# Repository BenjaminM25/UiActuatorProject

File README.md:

# Closed-Loop Linear Actuator

> Bachelor project, University of Agder (UiA), 2026
> Custom BLDC motor controller for a leadscrew linear actuator with
> closed-loop position control.

## Overview

This project contains code and production files for a small linear
actuator using the lead screw principle with a custom pcb. The system
consists of a 12 mm BLDC motor with a 1:24 gearbox, integrated hall-
sensors for motor commutation, a AS5600L magnetic encoder module for
position/velocity control. It also supports communication over CAN
and USB-C.

A demonstration video of the actuator can be found here:

[Demonstration video](https://youtube.com/watch?v=XubzCKECgCM)

## Features

- Trapezoidal 3-PWM/6-PWM commutation (Hall-sensor based)
- Closed-loop position control (profiled trajectory + PID)
- Phase current sensing via ADC
- On-chip temperature monitoring with thermal protection
- CAN (FDCAN) communication
- Live telemetry over USB CDC (Teleplotter)

## Hardware

| Component        | Part               |
|------------------|--------------------|
| MCU              | STM32G473RC        |
| Gate driver      | DRV8316 (SPI)      |
| Position encoder | AS5600L (I2C)      |
| Commutation      | Hall sensors       |
| CAN transceiver  | TCAN3403           |
| Motor            | 12 mm BLDC, 1:24   |

## Third Party

The DRV8316 BLDC Driver has been adapted from the[SIMPLEFOC](https://github.com/simplefoc/Arduino-FOC-drivers/tree/master/src/drivers/drv8316) GitHub library.

## Building & flashing

The CubeIDE project contains custom files for the actuator
within Core/Actuator. The DRV8316 driver, hall encoder and
magnetic encoder is found in Drivers/DRV8316.

The .elf file generated in Debug after building the project
is uploaded to the pcb using STM32CubeProgrammer. First time use
of the pcb requires either a ST-Link debugger using swd or
programming USB-C by setting the mcu in the
DFU(device firmware upgrade) mode.

## Disclaimer

Portions of this firmware were developed with the assistance of
AI-generated code. All such content has been reviewed, tested, and
adapted by the author.

## License
This project is licensed under the MIT License — see the [LICENSE](LICENSE) file.

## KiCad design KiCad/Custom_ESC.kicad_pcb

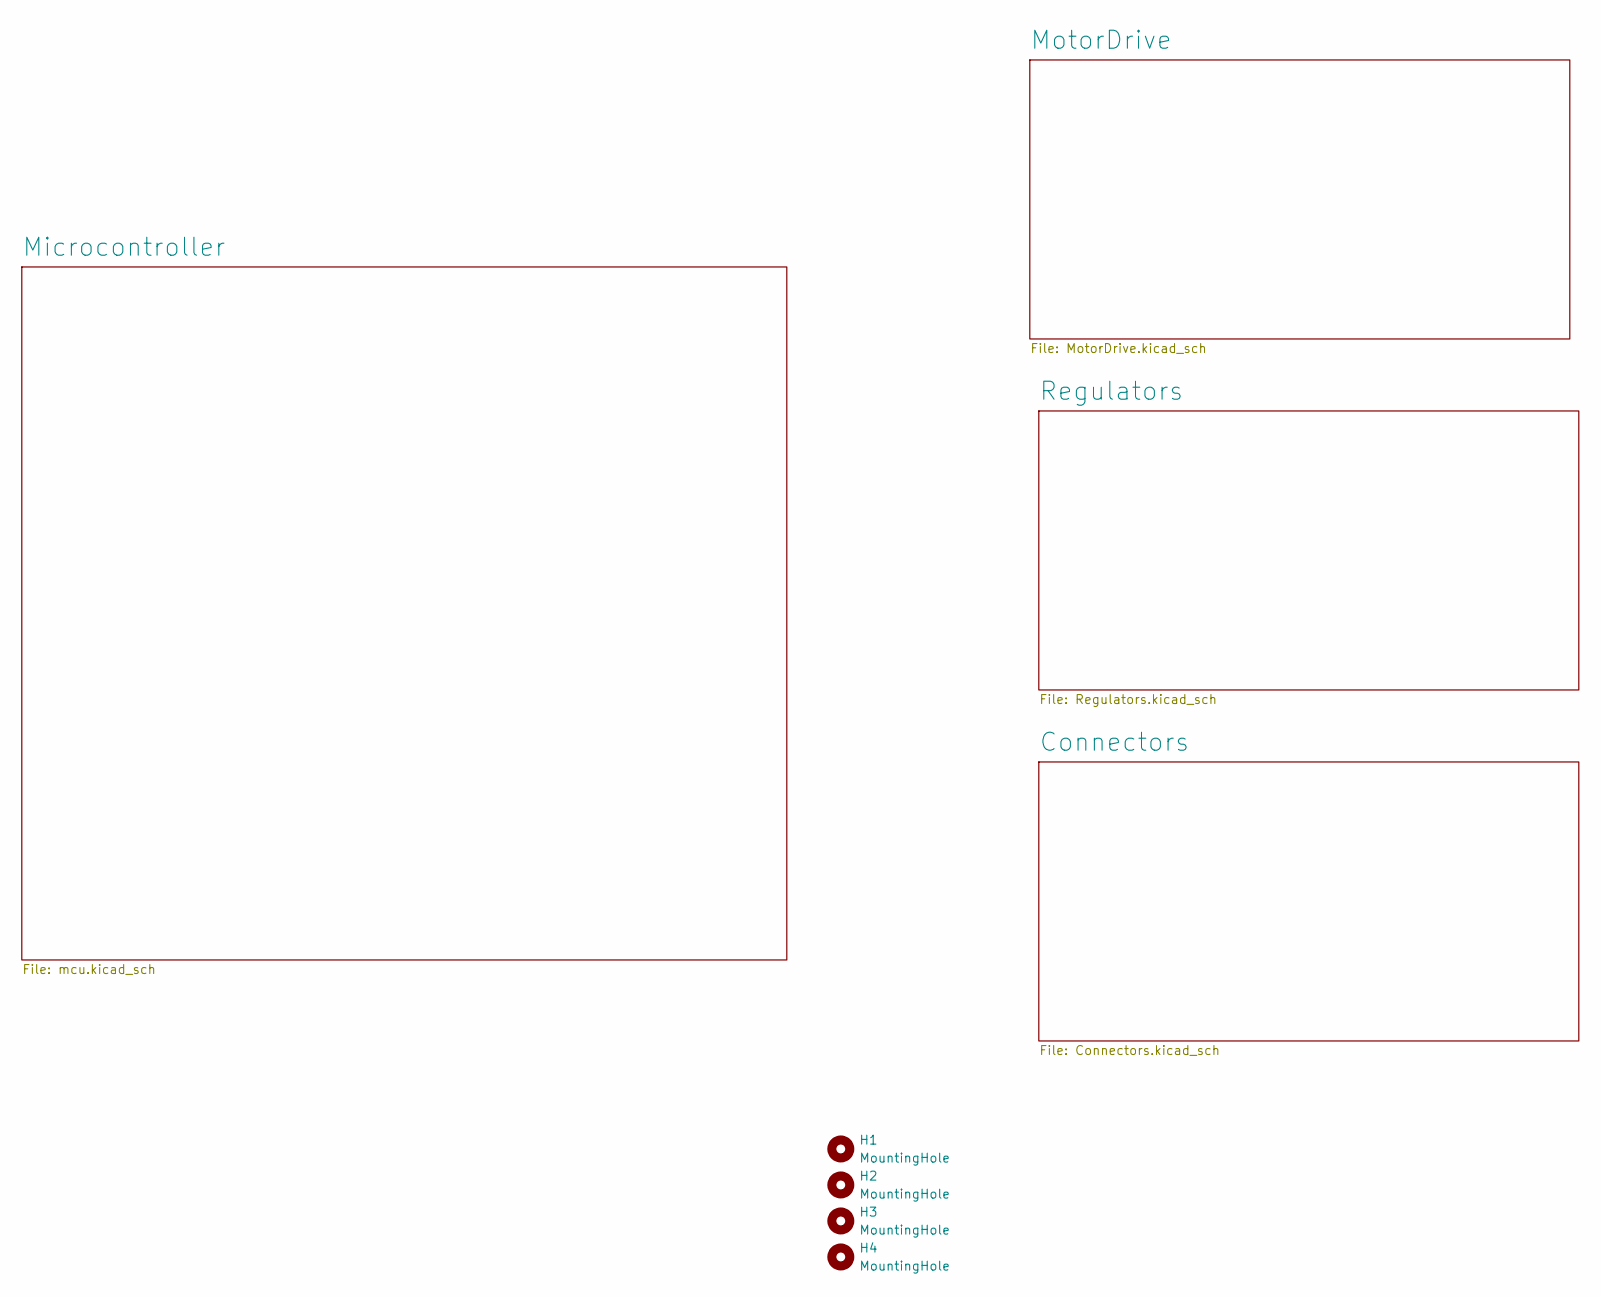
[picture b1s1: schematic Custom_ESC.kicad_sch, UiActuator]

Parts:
H1, H2, H3, H4: MountingHole; MountingHole_2.2mm_M2

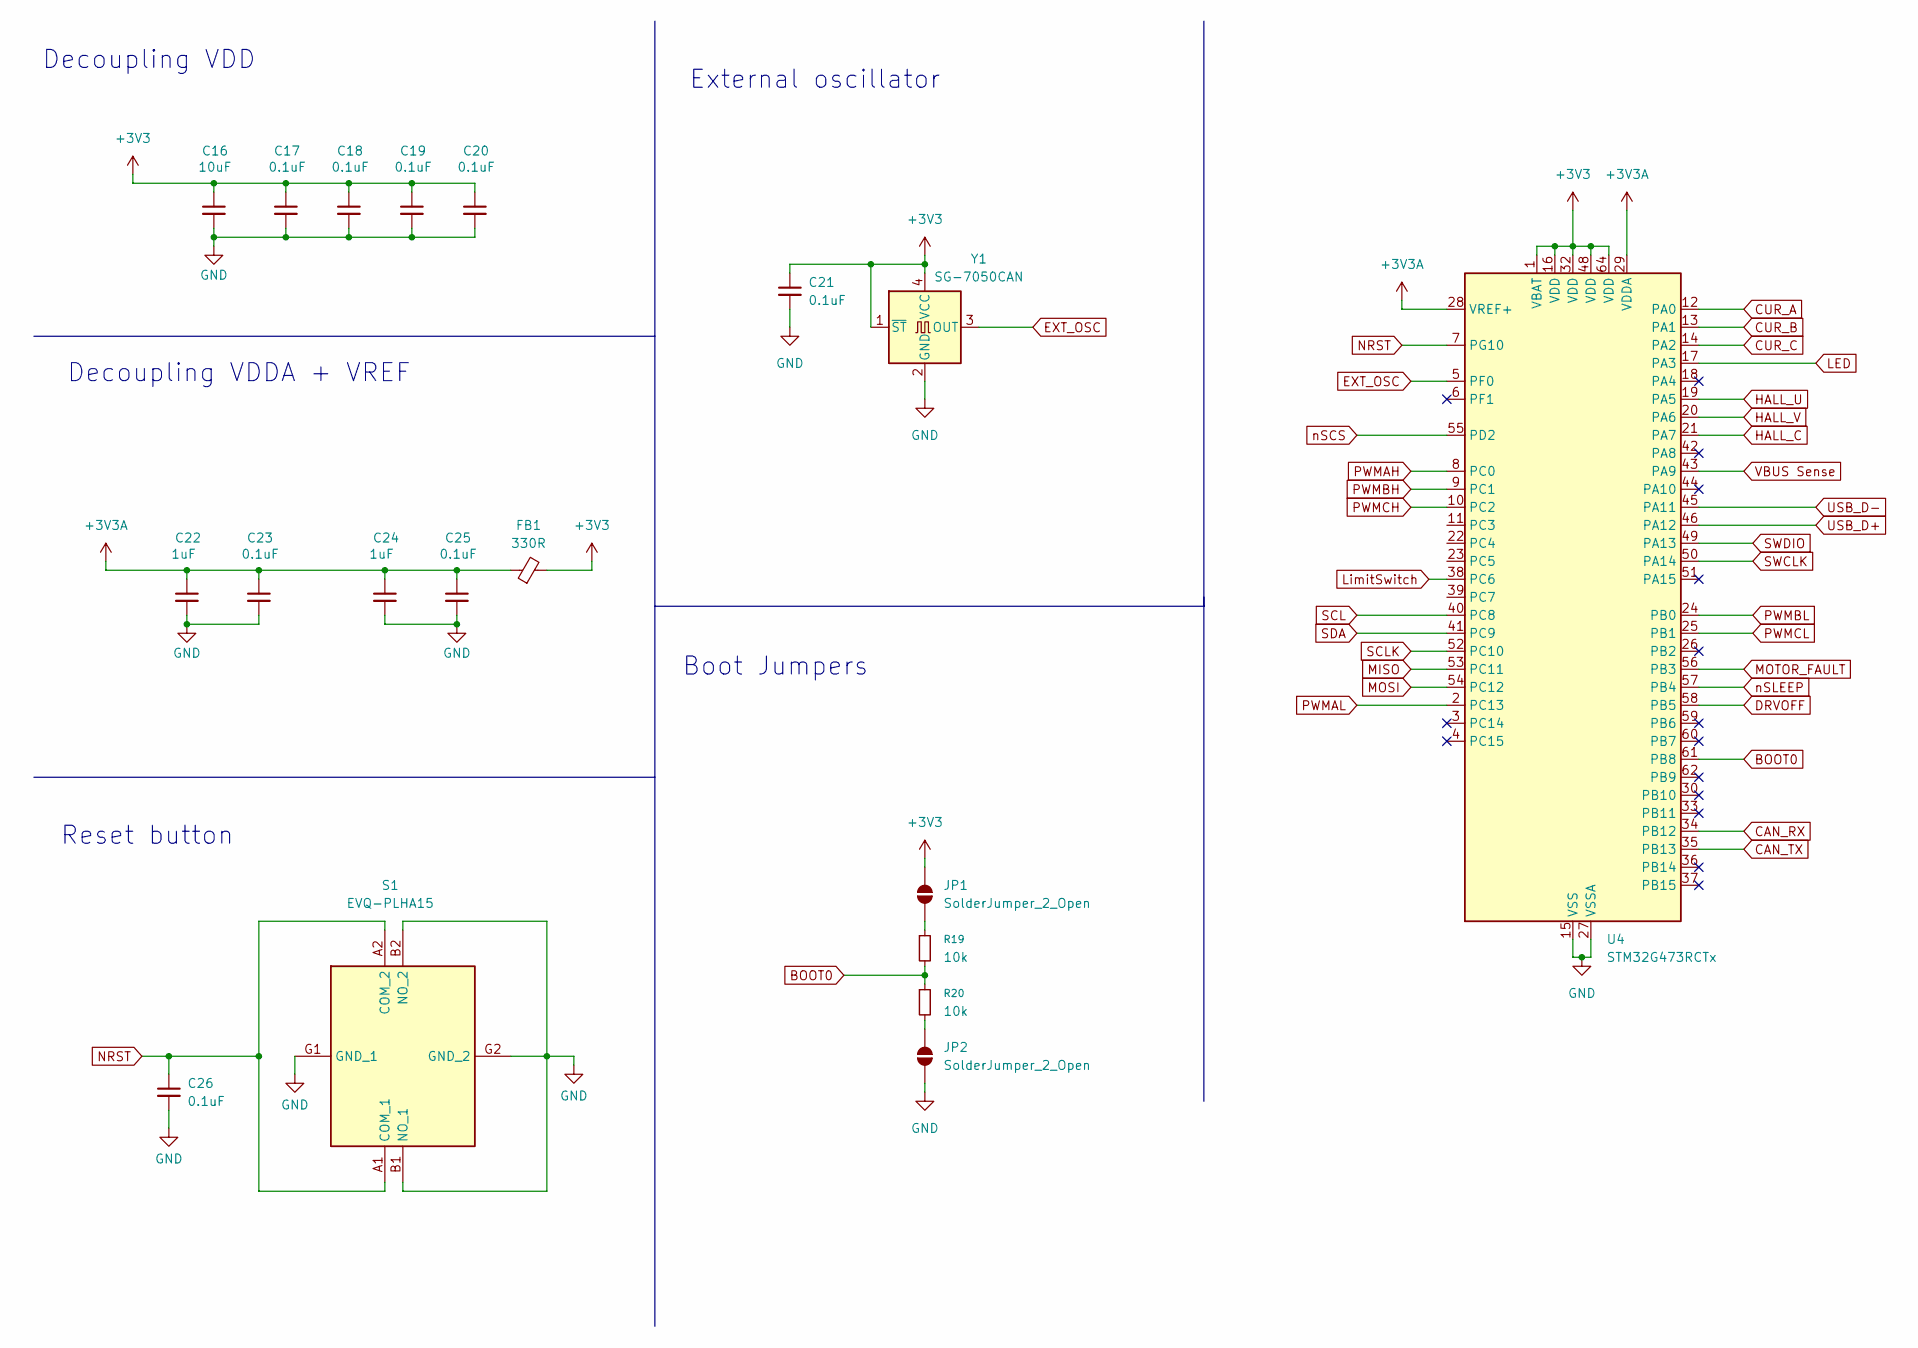
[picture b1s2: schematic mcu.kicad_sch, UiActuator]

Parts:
C16: 10uF; C_0603_1608Metric; LCSC C19702
C17, C18, C19, C20, C21, C23, C25, C26: 0.1uF; C_0402; LCSC C71687
C22, C24: 1uF; C_0402; LCSC C14445
FB1: 330R; L_0603; LCSC C113010
JP1, JP2: SolderJumper_2_Open; SolderJumper-2_P1.3mm_Open_RoundedPad1.0x1.5mm
R19, R20: 10k; R_0402; LCSC C60489
S1: EVQ-PLHA15; EVQPLHA15_pushbutton; Mouser Part Number 667-EVQ-PLHA15
U4: STM32G473RCTx; LQFP-64_10x10mm_P0.5mm; LCSC C529361
Y1: SG-7050CAN; X1G004481009712_EPS; LCSC C70513

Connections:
+3V3: C16.1, C17.1, C18.1, C19.1, C20.1, C21.1, FB1.2, JP1.2 (B), U4.1 (VBAT), U4.16 (VDD), U4.32 (VDD), U4.48 (VDD), U4.64 (VDD), Y1.1 (~ST), Y1.4 (VCC); also elsewhere on the board
+3V3A: C22.1, C23.1, C24.1, C25.1, FB1.1, U4.28 (VREF+), U4.29 (VDDA); also elsewhere on the board
BOOT0: R19.2, R20.1, U4.61 (PB8)
CAN_RX: U4.34 (PB12); also elsewhere on the board
CAN_TX: U4.35 (PB13); also elsewhere on the board
CUR_A: U4.12 (PA0); also elsewhere on the board
CUR_B: U4.13 (PA1); also elsewhere on the board
CUR_C: U4.14 (PA2); also elsewhere on the board
DRVOFF: U4.58 (PB5); also elsewhere on the board
EXT_OSC: U4.5 (PF0), Y1.3 (OUT)
GND: C16.2, C17.2, C18.2, C19.2, C20.2, C21.2, C22.2, C23.2, C24.2, C25.2, C26.2, JP2.1 (A), S1.B1 (NO_1), S1.B2 (NO_2), S1.G1 (GND_1), S1.G2 (GND_2), U4.15 (VSS), U4.27 (VSSA), U4.31 (VSS), U4.47 (VSS), U4.63 (VSS), Y1.2 (GND); also elsewhere on the board
HALL_C: U4.21 (PA7); also elsewhere on the board
HALL_U: U4.19 (PA5); also elsewhere on the board
HALL_V: U4.20 (PA6); also elsewhere on the board
LED: U4.17 (PA3); also elsewhere on the board
LimitSwitch: U4.38 (PC6); also elsewhere on the board
MISO: U4.53 (PC11); also elsewhere on the board
MOSI: U4.54 (PC12); also elsewhere on the board
MOTOR_FAULT: U4.56 (PB3); also elsewhere on the board
NRST: C26.1, S1.A1 (COM_1), S1.A2 (COM_2), U4.7 (PG10); also elsewhere on the board
unnamed: JP1.1 (A), R19.1
unnamed: JP2.2 (B), R20.2
PWMAH: U4.8 (PC0); also elsewhere on the board
PWMAL: U4.2 (PC13); also elsewhere on the board
PWMBH: U4.9 (PC1); also elsewhere on the board
PWMBL: U4.24 (PB0); also elsewhere on the board
PWMCH: U4.10 (PC2); also elsewhere on the board
PWMCL: U4.25 (PB1); also elsewhere on the board
SCL: U4.40 (PC8); also elsewhere on the board
SCLK: U4.52 (PC10); also elsewhere on the board
SDA: U4.41 (PC9); also elsewhere on the board
SWCLK: U4.50 (PA14); also elsewhere on the board
SWDIO: U4.49 (PA13); also elsewhere on the board
USB_D+: U4.46 (PA12); also elsewhere on the board
USB_D-: U4.45 (PA11); also elsewhere on the board
VBUS Sense: U4.43 (PA9); also elsewhere on the board
nSCS: U4.55 (PD2); also elsewhere on the board
nSLEEP: U4.57 (PB4); also elsewhere on the board

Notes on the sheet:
External oscillator
Decoupling VDD
Reset button
Boot Jumpers
Decoupling VDDA + VREF

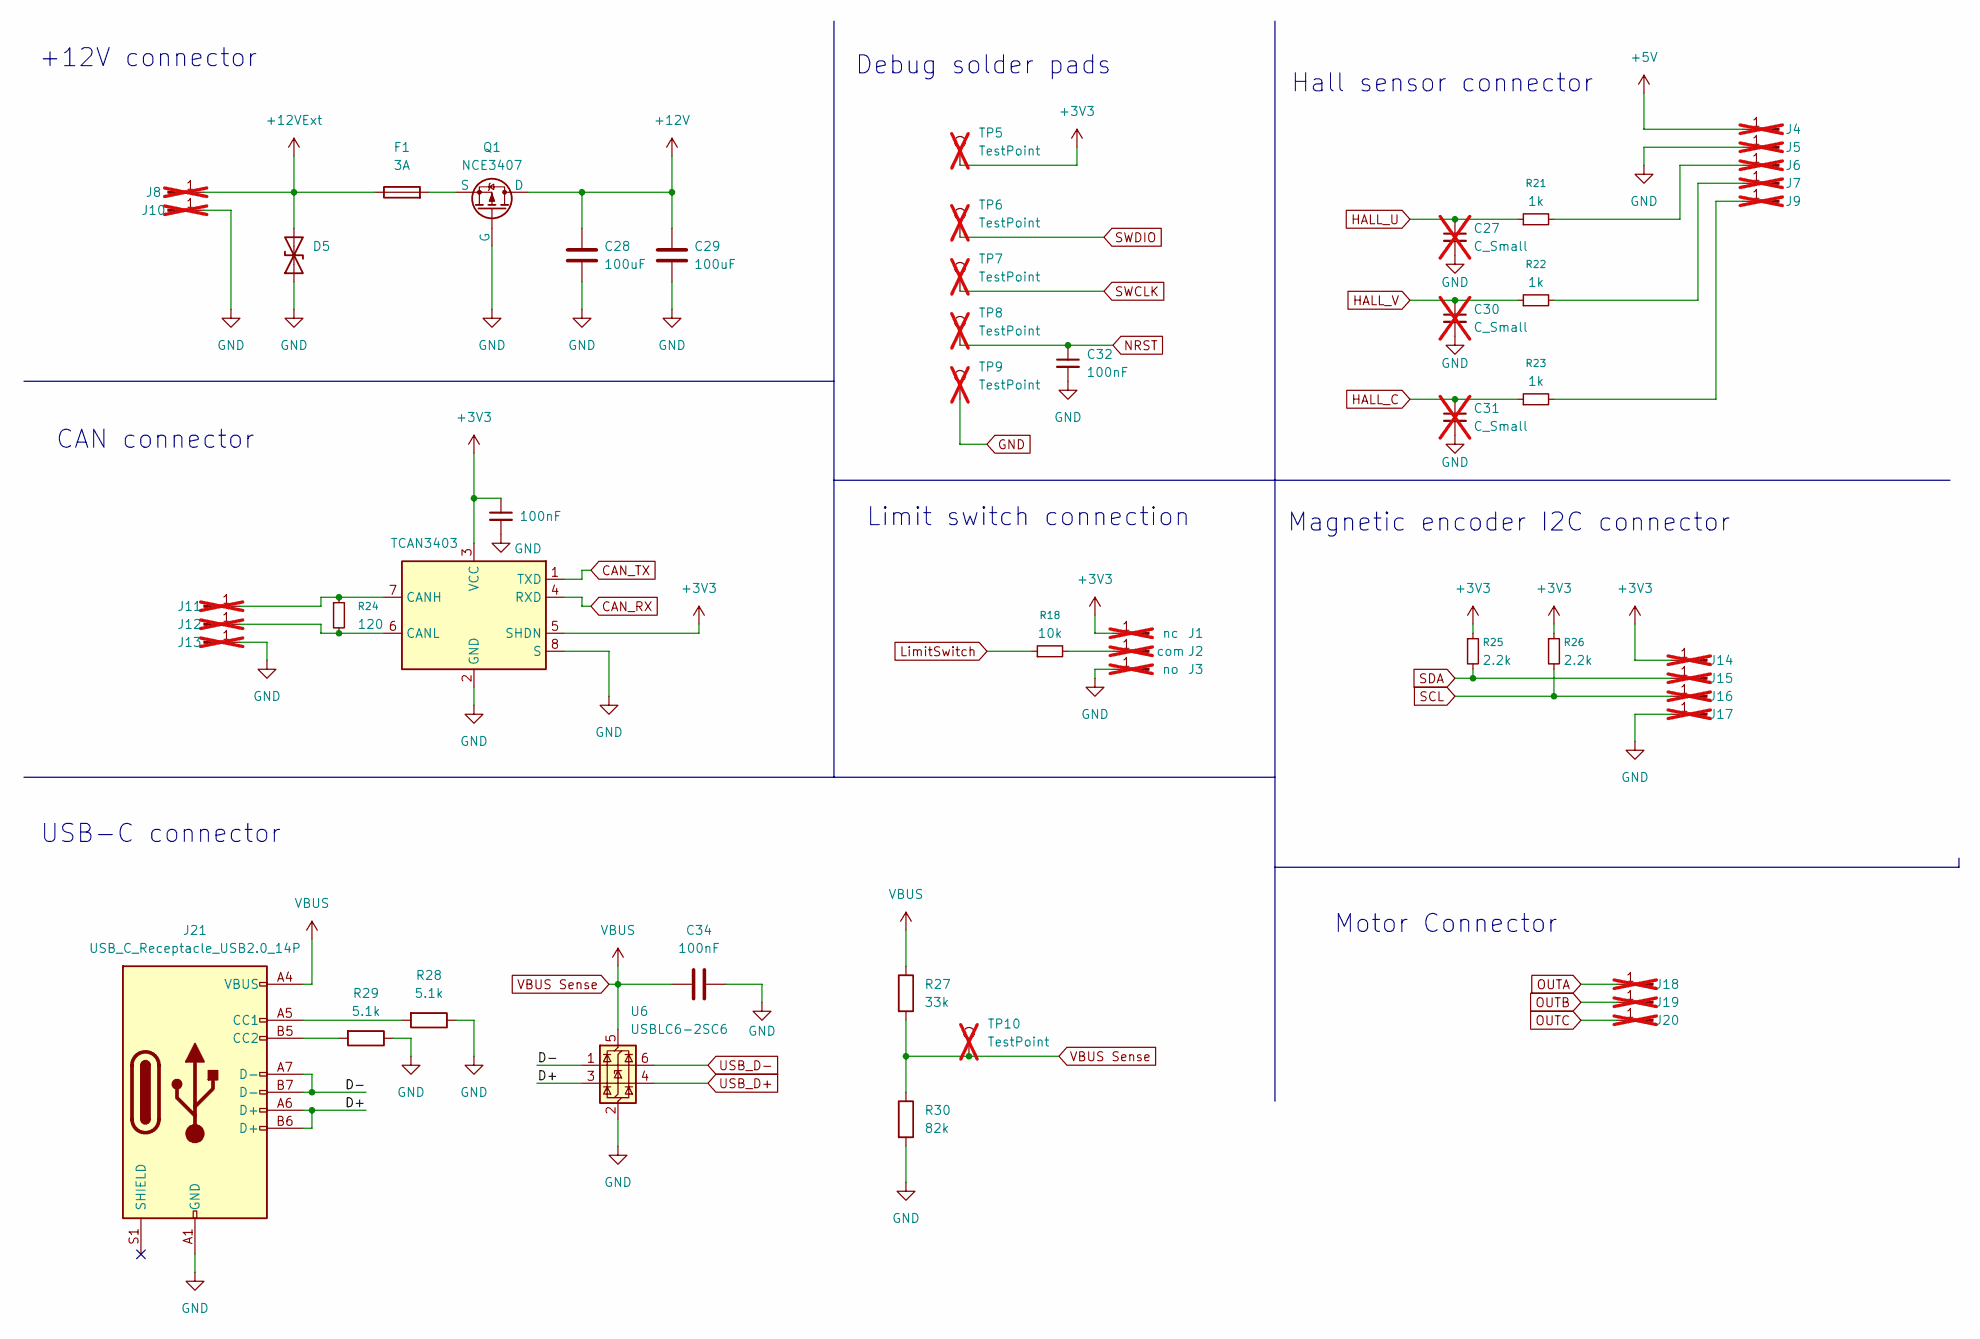
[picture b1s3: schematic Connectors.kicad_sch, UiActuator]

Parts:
C27, C30, C31: C_Small; C_0603; not fitted
C28, C29: 100uF; CAP_T55D_VIS; LCSC C215892
C32, C33, C34: 100nF; C_0402; LCSC C71687
D5: 13; D_SOD-123FL; LCSC C5353308
F1: 3A; FUSE_SMDF050-2; LCSC C135370
J1: nc; TestPoint_Pad_D1.0mm; not fitted
J2: com; TestPoint_Pad_D1.0mm; not fitted
J3: no; TestPoint_Pad_D1.0mm; not fitted
J4, J5, J6, J7, J9, J11, J12, J13, J14, J15, J16, J17, J18, J19, J20: A; SolderWirePad_1x01_SMD_1x2mm; not fitted
J8, J10: A; SolderWirePad_1x01_SMD_2x4mm; not fitted
J21: USB_C_Receptacle_USB2.0_14P; USB_C_Receptacle_GCT_USB4105-xx-A_16P_TopMnt_Horizontal; LCSC C2927038
Q1: NCE3407; SOT-23; LCSC C113770
R18: 10k; R_0402; LCSC C60489
R21, R22, R23: 1k; C_0603; LCSC C21190
R24: 120; R_0603; LCSC C22787
R25, R26: 2.2k; R_0402; LCSC C25879
R27: 33k; R_0402; LCSC C25779
R28, R29: 5.1k; R_0402; LCSC C25905
R30: 82k; R_0402; LCSC C4142
TP5, TP6, TP7, TP8, TP9, TP10: TestPoint; TestPoint_Pad_D1.0mm; not fitted
U5: TCAN3403; SOT-23-8_Handsoldering; LCSC C35926232
U6: USBLC6-2SC6; SOT-23-6; LCSC C7519

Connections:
+3V3: C33.1, J1.1, J14.1, R25.1, R26.1, TP5.1, U5.3 (VCC), U5.5 (SHDN); also elsewhere on the board
+5V: J4.1; also elsewhere on the board
+12V: C28.1, C29.1, Q1.3 (D); also elsewhere on the board
+12VExt: D5.2 (A2), F1.1, J8.1
/Connectors/D+: J21.A6 (D+), J21.B6 (D+), U6.3 (I/O2)
/Connectors/D-: J21.A7 (D-), J21.B7 (D-), U6.1 (I/O1)
CAN_RX: U5.4 (RXD); also elsewhere on the board
CAN_TX: U5.1 (TXD); also elsewhere on the board
GND: C27.2, C28.2, C29.2, C30.2, C31.2, C32.2, C33.2, C34.1, D5.1 (A1), J3.1, J5.1, J10.1, J13.1, J17.1, J21.A1 (GND), J21.A12 (GND), J21.B1 (GND), J21.B12 (GND), Q1.1 (G), R28.1, R29.1, R30.2, TP9.1, U5.2 (GND), U5.8 (S), U6.2 (GND); also elsewhere on the board
HALL_C: C31.1, R23.1; also elsewhere on the board
HALL_U: C27.1, R21.1; also elsewhere on the board
HALL_V: C30.1, R22.1; also elsewhere on the board
LimitSwitch: R18.1; also elsewhere on the board
NRST: C32.1, TP8.1; also elsewhere on the board
unnamed: J2.1, R18.2
unnamed: J6.1, R21.2
unnamed: J7.1, R22.2
unnamed: J9.1, R23.2
unnamed: J11.1, R24.1, U5.7 (CANH)
unnamed: J12.1, R24.2, U5.6 (CANL)
unnamed: J21.A5 (CC1), R28.2
unnamed: J21.B5 (CC2), R29.2
unnamed: F1.2, Q1.2 (S)
OUTA: J18.1; also elsewhere on the board
OUTB: J19.1; also elsewhere on the board
OUTC: J20.1; also elsewhere on the board
SCL: J16.1, R26.2; also elsewhere on the board
SDA: J15.1, R25.2; also elsewhere on the board
SWCLK: TP7.1; also elsewhere on the board
SWDIO: TP6.1; also elsewhere on the board
USB_D+: U6.4 (I/O2); also elsewhere on the board
USB_D-: U6.6 (I/O1); also elsewhere on the board
VBUS Sense: C34.2, J21.A4 (VBUS), J21.A9 (VBUS), J21.B4 (VBUS), J21.B9 (VBUS), R27.1, R27.2, R30.1, TP10.1, U6.5 (VBUS); also elsewhere on the board

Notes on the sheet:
USB-C connector
Hall sensor connector
CAN connector
Magnetic encoder I2C connector
Motor Connector
+12V connector
Limit switch connection
Debug solder pads

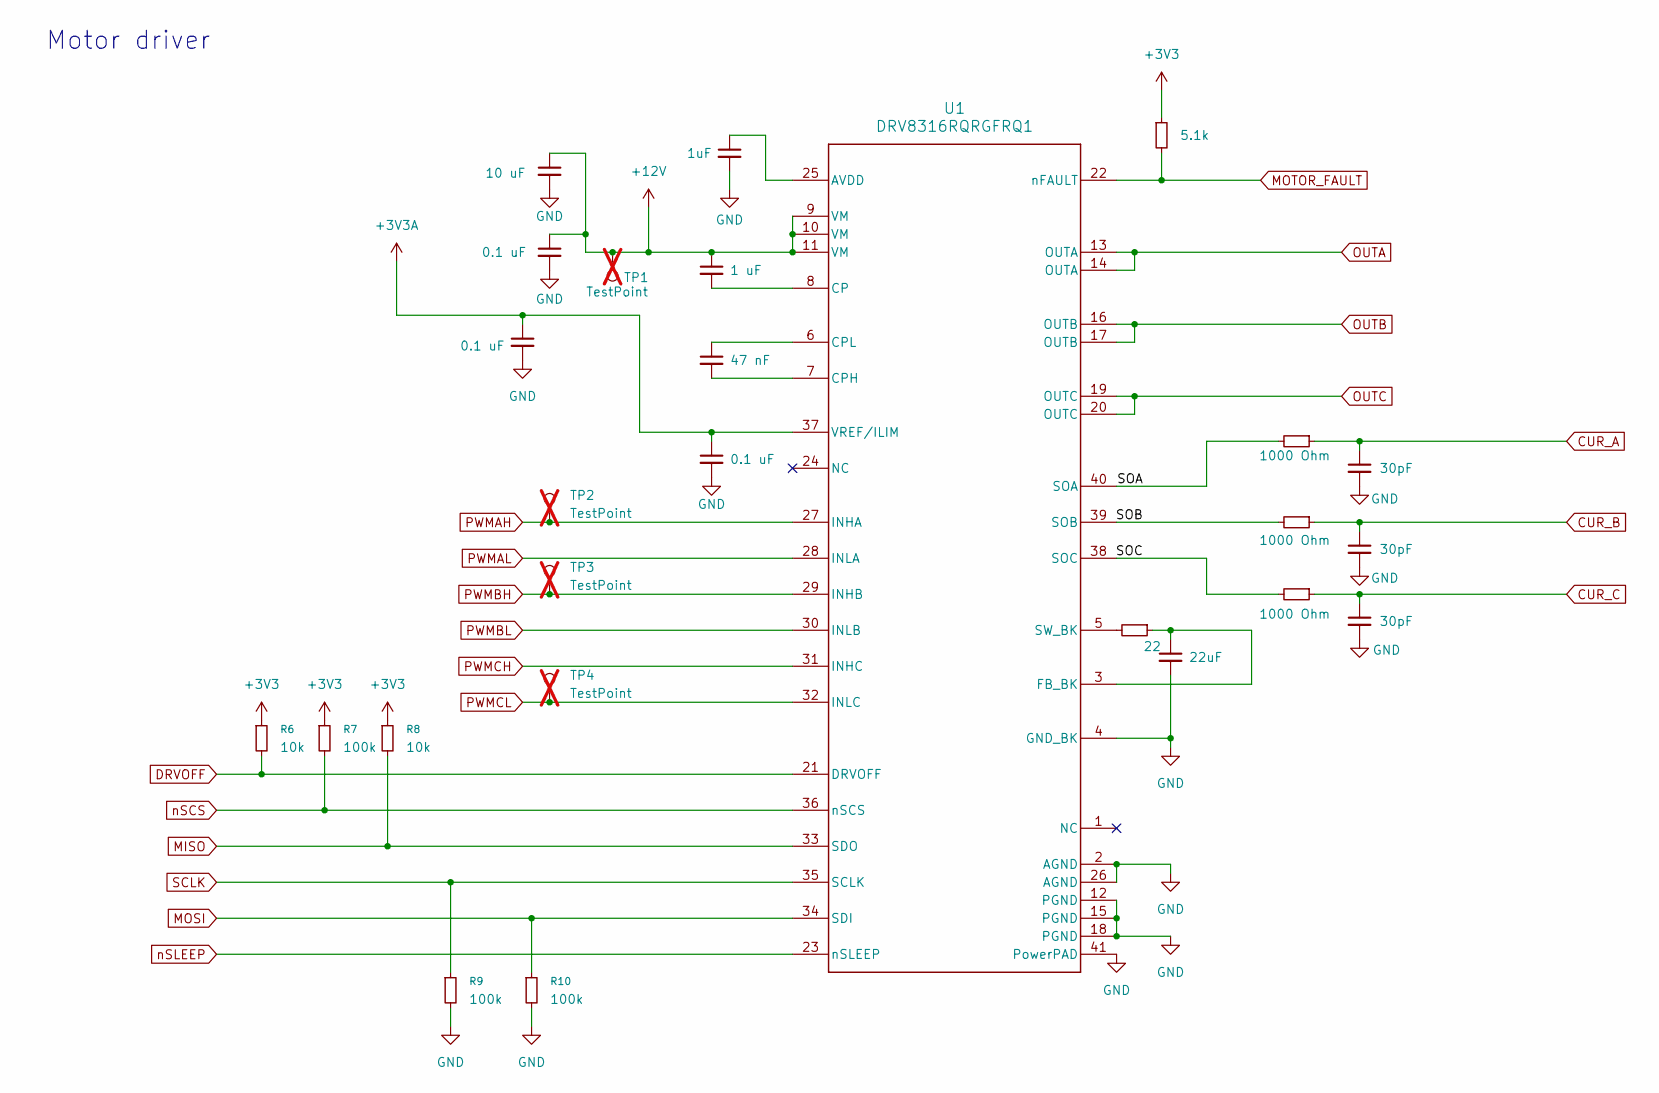
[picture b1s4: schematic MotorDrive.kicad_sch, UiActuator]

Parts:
C1: 1uF; C_0402; LCSC C14445
C2: 10 uF; C_0603_1608Metric; LCSC C96446
C3: 0.1 uF; C_0402; LCSC C56392
C4: 1 uF; C_0402; LCSC C52923
C5, C7: 0.1 uF; C_0402; LCSC C71687
C6: 47 nF; C_0402; LCSC C285062
C8, C9, C10: 30pF; C_0402; LCSC C107004
C11: 22uF; C_0603_1608Metric; LCSC C29519229
R1: 5.1k; R_0402; LCSC C25905
R2, R3, R4: 1000 Ohm; R_0402; LCSC C11702
R5: 22; R_0402; LCSC C25092
R6, R8: 10k; R_0402; LCSC C25531
R7, R9, R10: 100k; R_0402; LCSC C25530
TP1, TP2, TP3, TP4: TestPoint; TestPoint_Pad_D1.0mm; not fitted
U1: DRV8316RQRGFRQ1; RGF0040E-IPC_A; LCSC C5218859

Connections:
+3V3: R1.1, R6.1, R7.1, R8.1; also elsewhere on the board
+3V3A: C5.1, C7.1, U1.37 (VREF/ILIM); also elsewhere on the board
+12V: C2.1, C3.1, C4.1, TP1.1, U1.9 (VM), U1.10 (VM), U1.11 (VM); also elsewhere on the board
/MotorDrive/SOA: R2.2, U1.40 (SOA)
/MotorDrive/SOB: R3.2, U1.39 (SOB)
/MotorDrive/SOC: R4.2, U1.38 (SOC)
CUR_A: C8.1, R2.1; also elsewhere on the board
CUR_B: C9.1, R3.1; also elsewhere on the board
CUR_C: C10.1, R4.1; also elsewhere on the board
DRVOFF: R6.2, U1.21 (DRVOFF); also elsewhere on the board
GND: C1.2, C2.2, C3.2, C5.2, C7.2, C8.2, C9.2, C10.2, C11.2, R9.2, R10.2, U1.2 (AGND), U1.4 (GND_BK), U1.12 (PGND), U1.15 (PGND), U1.18 (PGND), U1.26 (AGND), U1.41 (PowerPAD); also elsewhere on the board
MISO: R8.2, U1.33 (SDO); also elsewhere on the board
MOSI: R10.1, U1.34 (SDI); also elsewhere on the board
MOTOR_FAULT: R1.2, U1.22 (nFAULT); also elsewhere on the board
unnamed: C1.1, U1.25 (AVDD)
unnamed: C4.2, U1.8 (CP)
unnamed: C6.2, U1.7 (CPH)
unnamed: C6.1, U1.6 (CPL)
unnamed: C11.1, R5.1, U1.3 (FB_BK)
unnamed: R5.2, U1.5 (SW_BK)
OUTA: U1.13 (OUTA), U1.14 (OUTA); also elsewhere on the board
OUTB: U1.16 (OUTB), U1.17 (OUTB); also elsewhere on the board
OUTC: U1.19 (OUTC), U1.20 (OUTC); also elsewhere on the board
PWMAH: TP2.1, U1.27 (INHA); also elsewhere on the board
PWMAL: U1.28 (INLA); also elsewhere on the board
PWMBH: TP3.1, U1.29 (INHB); also elsewhere on the board
PWMBL: U1.30 (INLB); also elsewhere on the board
PWMCH: U1.31 (INHC); also elsewhere on the board
PWMCL: TP4.1, U1.32 (INLC); also elsewhere on the board
SCLK: R9.1, U1.35 (SCLK); also elsewhere on the board
nSCS: R7.2, U1.36 (nSCS); also elsewhere on the board
nSLEEP: U1.23 (nSLEEP); also elsewhere on the board

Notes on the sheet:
Motor driver

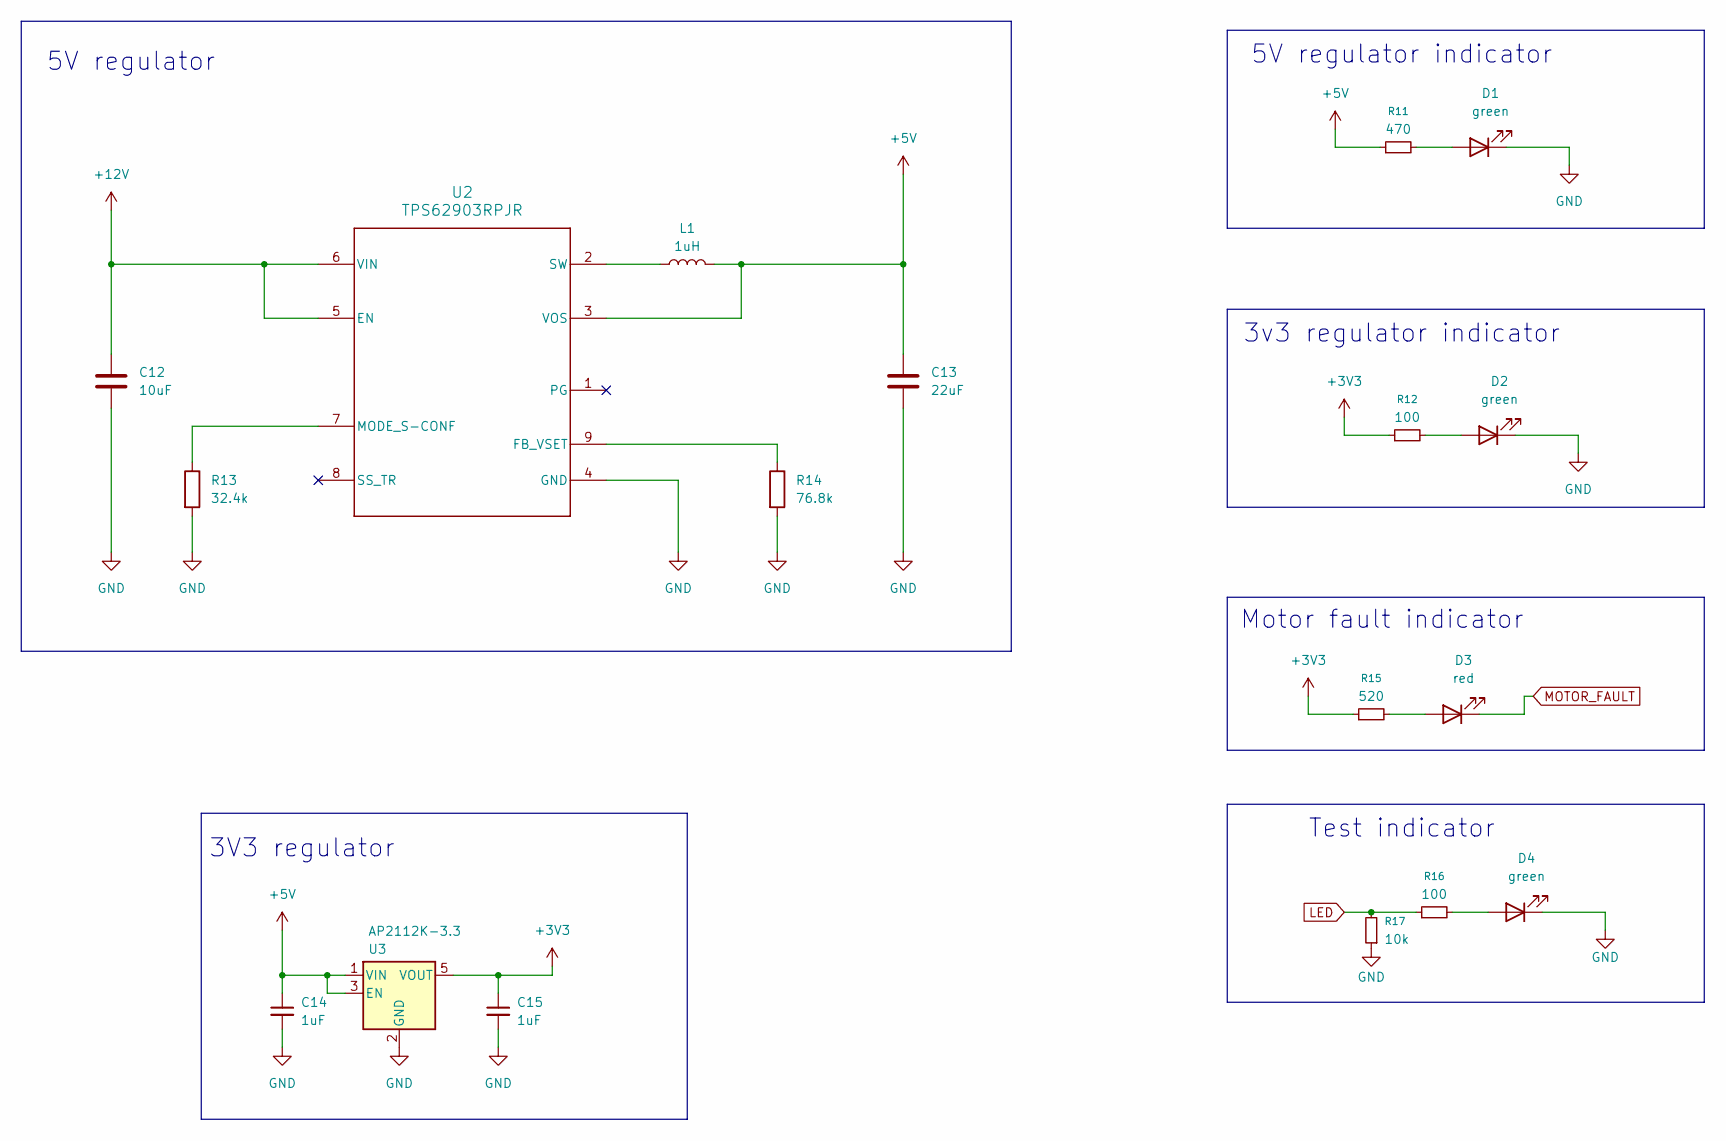
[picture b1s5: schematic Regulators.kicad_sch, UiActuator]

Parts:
C12: 10uF; C_0603_1608Metric; LCSC C96446
C13: 22uF; C_0603_1608Metric; LCSC C29519229
C14, C15: 1uF; C_0402; LCSC C14445
D1, D2, D4: green; LED_0603_1608Metric; LCSC C12624
D3: red; LED_0603_1608Metric; LCSC C2286
L1: 1uH; L_Coilcraft_XxL4020; LCSC C5357696
R11: 470; R_0402; LCSC C25117
R12, R16: 100; R_0402; LCSC C25076
R13: 32.4k; R_0402; LCSC C26974
R14: 76.8k; R_0402; LCSC C26987
R15: 520; R_0402; LCSC C25123
R17: 10k; R_0402; LCSC C60489
U2: TPS62903RPJR; TPS62903RPJRRPJ0009A; LCSC C2866502
U3: AP2112K-3.3; SOT-23-5; LCSC C51118

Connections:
+3V3: C15.1, R12.1, R15.1, U3.5 (VOUT); also elsewhere on the board
+5V: C13.1, C14.1, L1.2, R11.1, U2.3 (VOS), U3.1 (VIN), U3.3 (EN); also elsewhere on the board
+12V: C12.1, U2.5 (EN), U2.6 (VIN); also elsewhere on the board
GND: C12.2, C13.2, C14.2, C15.2, D1.1 (K), D2.1 (K), D4.1 (K), R13.2, R14.2, R17.1, U2.4 (GND), U3.2 (GND); also elsewhere on the board
LED: R16.1, R17.2; also elsewhere on the board
MOTOR_FAULT: D3.1 (K); also elsewhere on the board
unnamed: D1.2 (A), R11.2
unnamed: D2.2 (A), R12.2
unnamed: D3.2 (A), R15.2
unnamed: D4.2 (A), R16.2
unnamed: R14.1, U2.9 (FB_VSET)
unnamed: R13.1, U2.7 (MODE_S-CONF)
unnamed: L1.1, U2.2 (SW)

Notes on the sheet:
3v3 regulator indicator
Motor fault indicator
5V regulator
3V3 regulator
Test indicator
5V regulator indicator

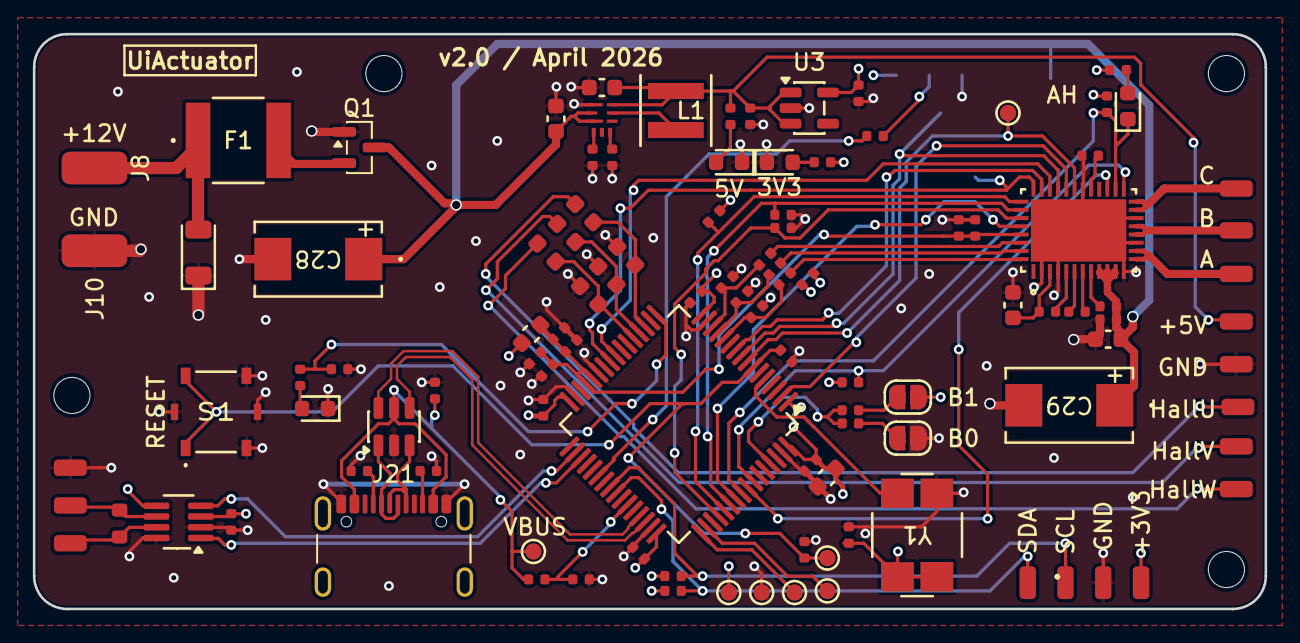
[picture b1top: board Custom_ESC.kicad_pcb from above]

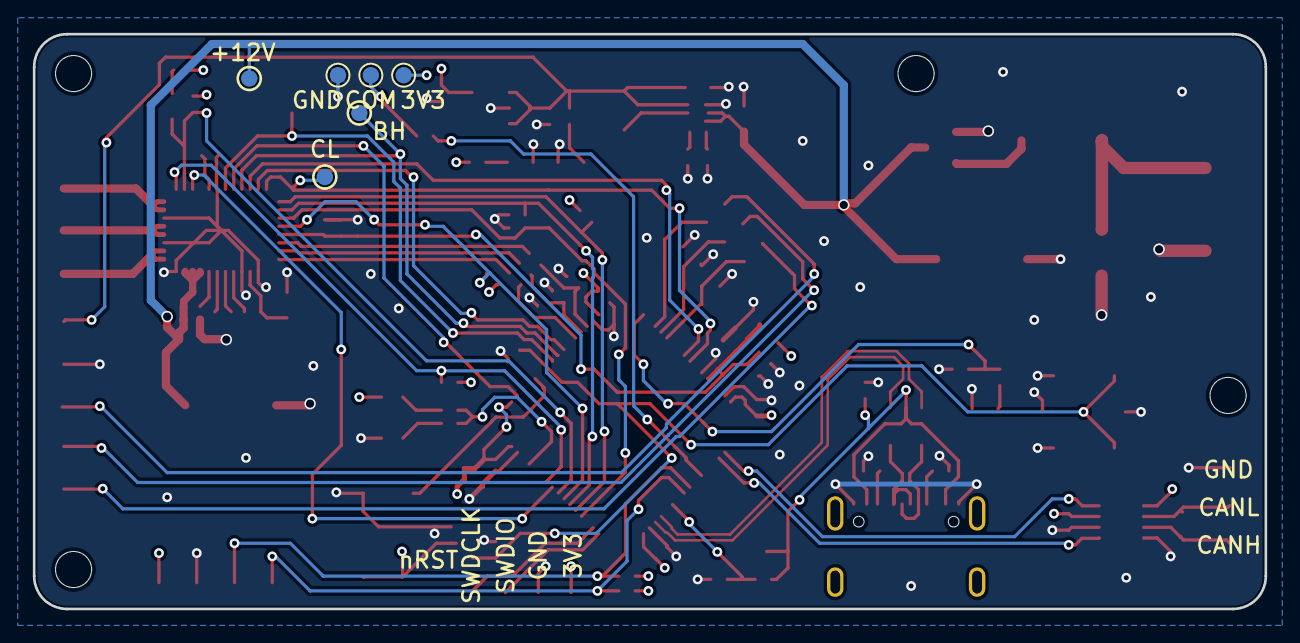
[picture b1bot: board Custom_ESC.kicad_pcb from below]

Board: 4 copper layers, 75.0 x 35.0 mm, 118 parts (6 on the bottom side), 71 nets.

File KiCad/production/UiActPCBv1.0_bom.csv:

Designator,Footprint,Quantity,Value,LCSC Part #
"C1, C14, C15, C22, C24",C_0402,5,1uF,C14445
"C10, C8, C9",C_0402,3,30pF,C107004
"C11, C13",0603,2,22uF,C29519229
C12,0603,1,10uF,C96446
C16,0603,1,10uF,C19702
"C17, C18, C19, C20, C21, C23, C25, C26",C_0402,8,0.1uF,C71687
C2,0603,1,10 uF,C96446
C27,CAP_EEF_CX_PAN,1,EEF-CX0D221R,C165968
C3,C_0402,1,0.1 uF,C56392
"C31, C32, C33",C_0402,3,100nF,C71687
C4,C_0402,1,1 uF,C52923
"C5, C7",C_0402,2,0.1 uF,C71687
C6,C_0402,1,47 nF,C285062
"D1, D2, D4",0603,3,green,C12624
D3,0603,1,red,C2286
D5,VS12VBA1HST15R,1,VS12VBA1HST15R,C3711499
F1,FUSE_SMDF050-2,1,Fuse,C135370
FB1,L_0603,1,330R,C113010
J21,USB_C_Receptacle_GCT_USB4105-xx-A_16P_TopMnt_Horizontal,1,USB_C_Receptacle_USB2.0_14P,C2927038
L1,L_Coilcraft_XxL4020,1,1u,C5357696
Q1,SOT-23,1,NCE3407,C113770
"R1, R28, R29",R_0402,3,5.1k,C25905
"R10, R7, R9",R_0402,3,100k,C25530
R11,R_0402,1,200k,C25764
R12,R_0402,1,470,C25117
"R13, R16",R_0402,2,100,C25076
R14,R_0402,1,76.8k,C26987
R15,R_0402,1,520,C25123
"R17, R18, R19, R20",R_0402,4,10k,C60489
"R2, R3, R4",R_0402,3,1000 Ohm,C11702
R24,R_0603,1,120,C25079
"R25, R26",R_0402,2,40k,C25783
R27,R_0402,1,33k,C25779
R30,R_0402,1,82k,C4142
R5,R_0402,1,22,C25092
"R6, R8",R_0402,2,10k,C25531
S1,EVQPLHA15_pushbutton,1,EVQ-PLHA15,C79172
U1,RGF0040E-IPC_A,1,DRV8316RQRGFRQ1,C5218859
U2,TPS62903RPJRRPJ0009A,1,TPS62903RPJR,C2866502
U3,SOT-23-5,1,AP2112K-3.3,C51118
U4,LQFP-64_10x10mm_P0.5mm,1,STM32G473RCTx, C529361
U5,SOT-23-8_Handsoldering,1,TCAN3403,C35926232
U6,SOT-23-6,1,USBLC6-2SC6,C7519
Y1,X1G004481009712_EPS,1,SG-7050CAN,C70513

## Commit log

2026-05-22 Added gitattributes and gitignore with LFS config
2026-05-22 Initial import of bachelor project files
2026-05-22 Initial commit of README for Closed-Loop Linear Actuator
    Added detailed project description, features, hardware components, and instructions for building and flashing the actuator.
2026-05-22 Add MIT License to the project
